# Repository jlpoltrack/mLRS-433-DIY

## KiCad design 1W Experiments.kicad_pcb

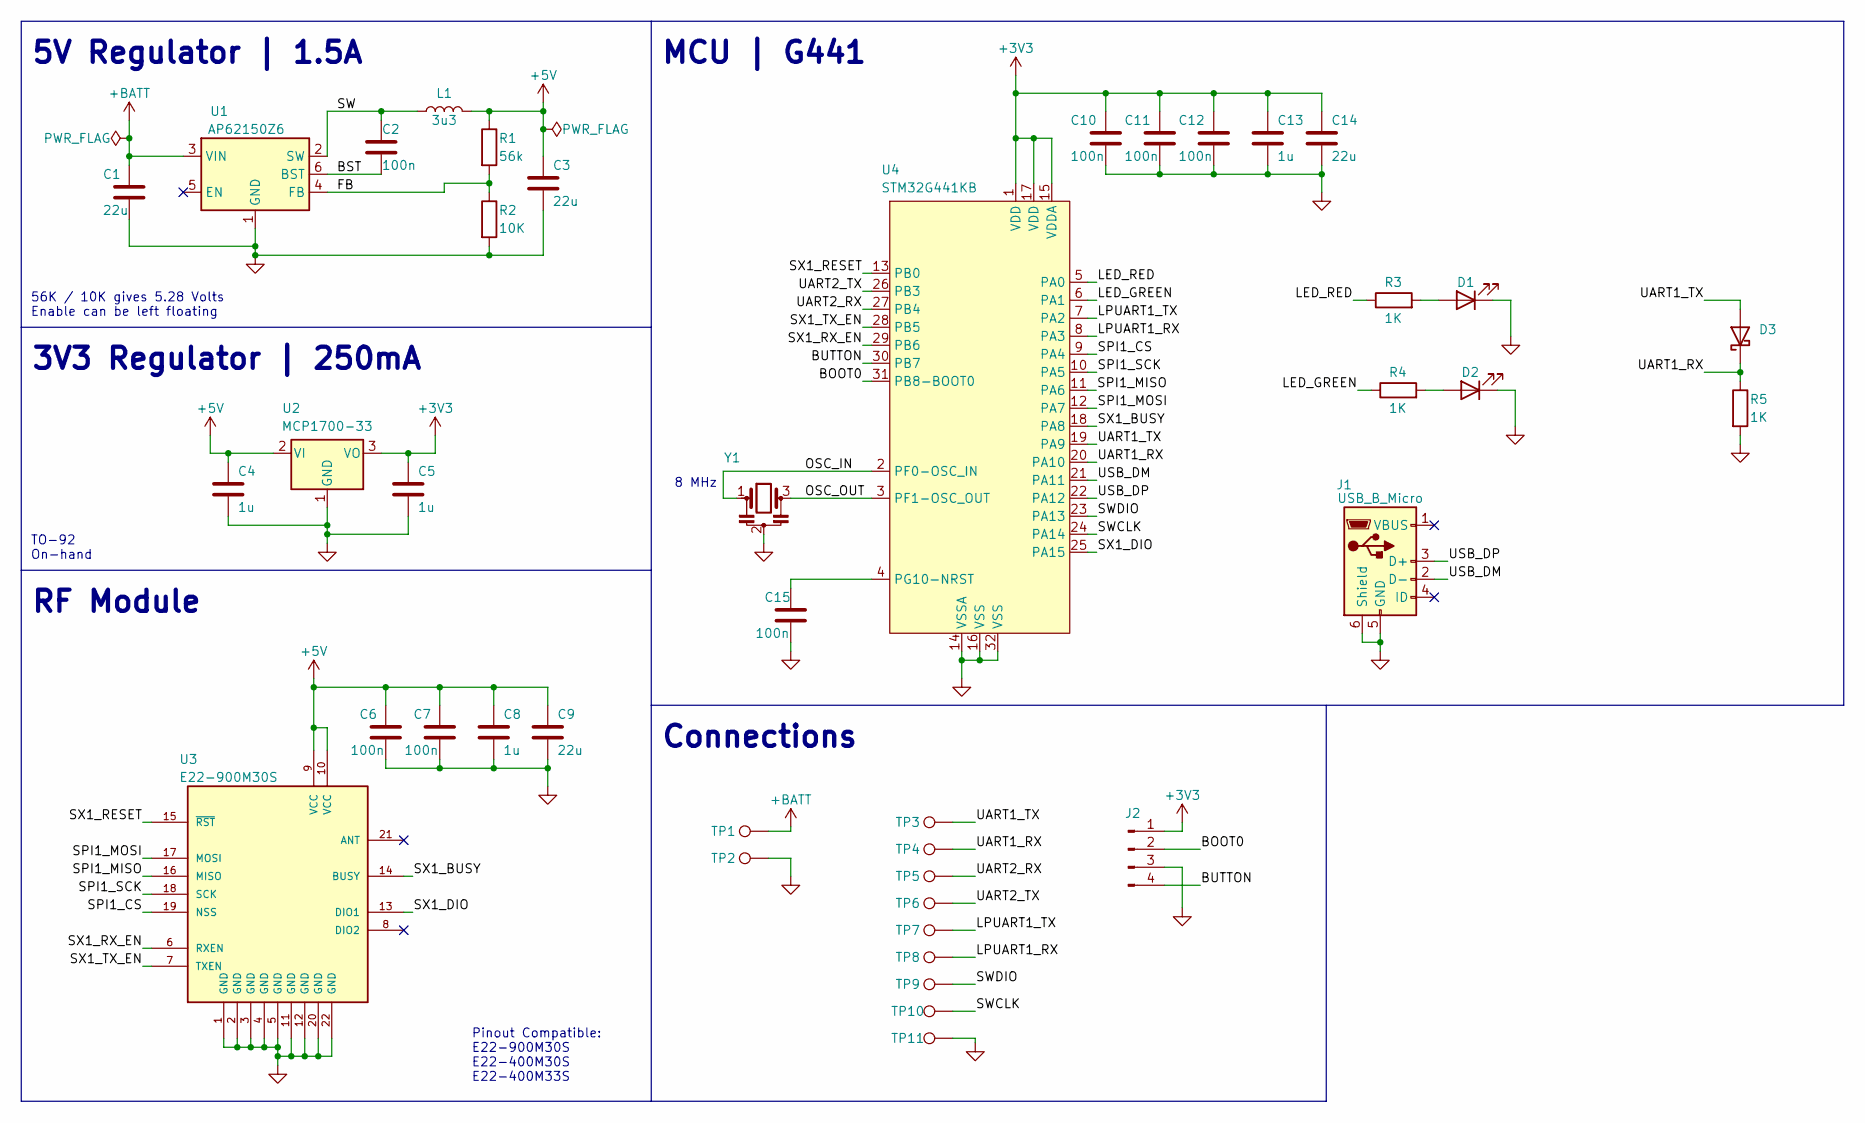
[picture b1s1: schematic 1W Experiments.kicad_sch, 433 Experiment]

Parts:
C1, C3, C9, C14: 22u; C_0805_2012Metric_Pad1.18x1.45mm_HandSolder
C2, C6, C7, C10, C11, C12, C15: 100n; C_0603_1608Metric_Pad1.08x0.95mm_HandSolder
C4, C5, C8, C13: 1u; C_0805_2012Metric_Pad1.18x1.45mm_HandSolder
D1, D2: LED; LED_0603_1608Metric_Pad1.05x0.95mm_HandSolder
D3: D_Schottky; D_SOD-323_HandSoldering
J1: USB_B_Micro; USB_Micro-B_Amphenol_10118194_Horizontal
J2: Conn_01x04_Male; PinHeader_1x04_P2.54mm_Vertical
L1: 3u3; L_1008_2520Metric_Pad1.43x2.20mm_HandSolder
R1: 56k; R_0603_1608Metric_Pad0.98x0.95mm_HandSolder
R2: 10K; R_0603_1608Metric_Pad0.98x0.95mm_HandSolder
R3, R4, R5: 1K; R_0603_1608Metric_Pad0.98x0.95mm_HandSolder
TP1, TP2, TP3, TP4, TP5, TP6, TP7, TP8: TestPoint; TestPoint_Pad_4.0x4.0mm
TP9, TP10, TP11: TestPoint; TestPoint_Pad_D2.5mm
U1: AP62150Z6; TSOT-23-6_HandSoldering
U2: MCP1700-33; TO-92_Inline
U3: E22-900M30S; XCVR_E22-900M30S; PARTREV 1.2
U4: STM32G441KB; LQFP-32_7x7mm_P0.8mm
Y1: Resonator; Resonator_SMD_Murata_CSTxExxV-3Pin_3.0x1.1mm_HandSoldering

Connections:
+3V3: C5.1, C10.1, C11.1, C12.1, C13.1, C14.1, J2.1, U2.3 (VO), U4.1 (VDD), U4.15 (VDDA), U4.17 (VDD)
+5V: C3.1, C4.1, C6.1, C7.1, C8.1, C9.1, L1.2, R1.1, U2.2 (VI), U3.9 (VCC), U3.10 (VCC)
+BATT: C1.1, TP1.1, U1.3 (VIN)
/BOOT0: J2.2, U4.31 (PB8-BOOT0)
/BST: C2.2, U1.6 (BST)
/BUTTON: J2.4, U4.30 (PB7)
/FB: R1.2, R2.1, U1.4 (FB)
/LED_GREEN: R4.1, U4.6 (PA1)
/LED_RED: R3.1, U4.5 (PA0)
/LPUART1_RX: TP8.1, U4.8 (PA3)
/LPUART1_TX: TP7.1, U4.7 (PA2)
/OSC_IN: U4.2 (PF0-OSC_IN), Y1.1
/OSC_OUT: U4.3 (PF1-OSC_OUT), Y1.3
/SPI1_CS: U3.19 (NSS), U4.9 (PA4)
/SPI1_MISO: U3.16 (MISO), U4.11 (PA6)
/SPI1_MOSI: U3.17 (MOSI), U4.12 (PA7)
/SPI1_SCK: U3.18 (SCK), U4.10 (PA5)
/SW: C2.1, L1.1, U1.2 (SW)
/SWCLK: TP10.1, U4.24 (PA14)
/SWDIO: TP9.1, U4.23 (PA13)
/SX1_BUSY: U3.14 (BUSY), U4.18 (PA8)
/SX1_DIO: U3.13 (DIO1), U4.25 (PA15)
/SX1_RESET: U3.15 (~RST), U4.13 (PB0)
/SX1_RX_EN: U3.6 (RXEN), U4.29 (PB6)
/SX1_TX_EN: U3.7 (TXEN), U4.28 (PB5)
/UART1_RX: D3.1 (K), R5.1, TP4.1, U4.20 (PA10)
/UART1_TX: D3.2 (A), TP3.1, U4.19 (PA9)
/UART2_RX: TP5.1, U4.27 (PB4)
/UART2_TX: TP6.1, U4.26 (PB3)
/USB_DM: J1.2 (D-), U4.21 (PA11)
/USB_DP: J1.3 (D+), U4.22 (PA12)
GND: C1.2, C3.2, C4.2, C5.2, C6.2, C7.2, C8.2, C9.2, C10.2, C11.2, C12.2, C13.2, C14.2, C15.2, D1.1 (K), D2.1 (K), J1.5 (GND), J1.6 (Shield), J2.3, R2.2, R5.2, TP2.1, TP11.1, U1.1 (GND), U2.1 (GND), U3.1 (GND), U3.2 (GND), U3.3 (GND), U3.4 (GND), U3.5 (GND), U3.11 (GND), U3.12 (GND), U3.20 (GND), U3.22 (GND), U4.14 (VSSA), U4.16 (VSS), U4.32 (VSS), Y1.2
unnamed: C15.1, U4.4 (PG10-NRST)
unnamed: D1.2 (A), R3.2
unnamed: D2.2 (A), R4.2

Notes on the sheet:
56K / 10K gives 5.28 Volts Enable can be left floating
Connections
Pinout Compatible: E22-900M30S E22-400M30S E22-400M33S
5V Regulator | 1.5A
3V3 Regulator | 250mA
8 MHz
MCU | G441
RF Module
TO-92 On-hand

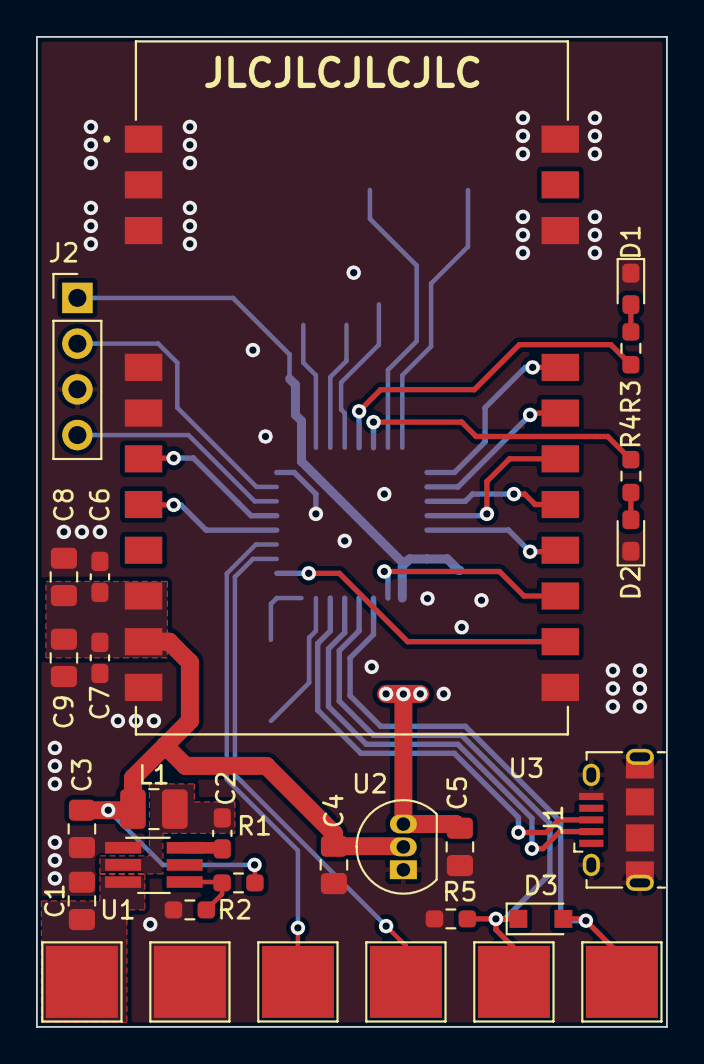
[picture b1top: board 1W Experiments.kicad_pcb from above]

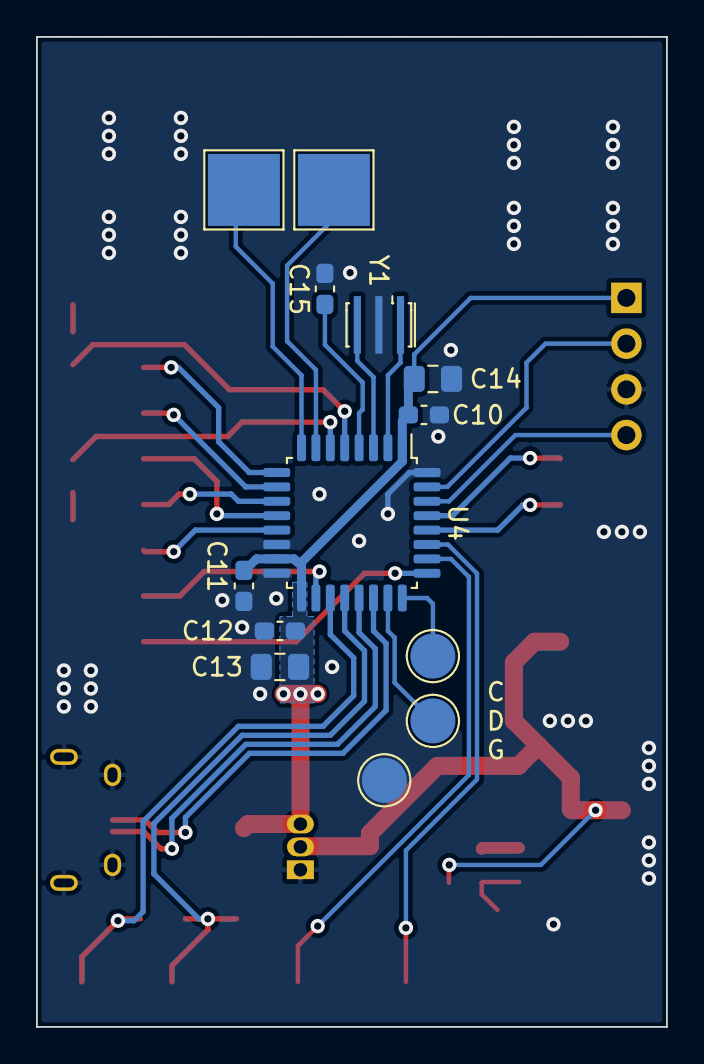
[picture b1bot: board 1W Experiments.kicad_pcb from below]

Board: 2 copper layers, 35.0 x 55.0 mm, 42 parts (13 on the bottom side), 35 nets.

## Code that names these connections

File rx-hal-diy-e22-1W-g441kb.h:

//*******************************************************
// Copyright (c) MLRS project
// GPL3
// https://www.gnu.org/licenses/gpl-3.0.de.html
// OlliW @ www.olliw.eu
//*******************************************************
// hal
//********************************************************

//-------------------------------------------------------
// RX DIY E22 v007 STM32G441KB
//-------------------------------------------------------

#define DEVICE_HAS_OUT


//-- Timers, Timing, EEPROM, and such stuff

#define DELAY_USE_DWT

#define SYSTICK_TIMESTEP          1000
#define SYSTICK_DELAY_MS(x)       (uint16_t)(((uint32_t)(x)*(uint32_t)1000)/SYSTICK_TIMESTEP)

#define EE_START_PAGE             60 // 128 kB flash, 2 kB page


//-- UARTS
// UARTB = serial port
// UART = output port, SBus or whatever
// UARTC = debug port

#define UARTB_USE_UART2_REMAPPED2 // serial
#define UARTB_BAUD                TX_SERIAL_BAUDRATE
#define UARTB_USE_TX
#define UARTB_TXBUFSIZE           TX_SERIAL_TXBUFSIZE
#define UARTB_USE_TX_ISR
#define UARTB_USE_RX
#define UARTB_RXBUFSIZE           TX_SERIAL_RXBUFSIZE
//#define UARTB_USE_RX_IO           IO_PA15 // normally would be PB4!!  Fixed in hardware

#define UART_USE_UART1                      // out pin
#define UART_BAUD                 100000    // SBus normal baud rate, is being set later anyhow
#define UART_USE_TX
#define UART_TXBUFSIZE            256       // 512
#define UART_USE_TX_ISR
//#define UART_USE_RX
//#define UART_RXBUFSIZE            512

#define UARTC_USE_LPUART1 // debug
#define UARTC_BAUD                115200
#define UARTC_USE_TX
#define UARTC_TXBUFSIZE           512
#define UARTC_USE_TX_ISR
//#define UARTC_USE_RX
//#define UARTC_RXBUFSIZE           512


//-- SX1: SX12xx & SPI

#define SPI_USE_SPI1              // PA5, PA6, PA7
#define SPI_CS_IO                 IO_PA4
#define SPI_USE_CLK_LOW_1EDGE     // datasheet says CPHA = 0  CPOL = 0
#define SPI_USE_CLOCKSPEED_9MHZ

#define SX_RESET                  IO_PB0
#define SX_DIO1                   IO_PB4
#define SX_BUSY                   IO_PA8
#define SX_RX_EN                  IO_PB6
#define SX_TX_EN                  IO_PB5

#define SX_DIO1_SYSCFG_EXTI_PORTx     LL_SYSCFG_EXTI_PORTB
#define SX_DIO1_SYSCFG_EXTI_LINEx     LL_SYSCFG_EXTI_LINE4
#define SX_DIO_EXTI_LINE_x            LL_EXTI_LINE_4
#define SX_DIO_EXTI_IRQn              EXTI4_IRQn
#define SX_DIO_EXTI_IRQHandler        EXTI4_IRQHandler
//#define SX_DIO_EXTI_IRQ_PRIORITY    11

void sx_init_gpio(void)
{
    gpio_init(SX_RESET, IO_MODE_OUTPUT_PP_HIGH, IO_SPEED_VERYFAST);
    gpio_init(SX_DIO1, IO_MODE_INPUT_PD, IO_SPEED_VERYFAST);
    gpio_init(SX_BUSY, IO_MODE_INPUT_PU, IO_SPEED_VERYFAST);
    gpio_init(SX_TX_EN, IO_MODE_OUTPUT_PP_LOW, IO_SPEED_VERYFAST);
    gpio_init(SX_RX_EN, IO_MODE_OUTPUT_PP_LOW, IO_SPEED_VERYFAST);
}

bool sx_busy_read(void)
{
    return (gpio_read_activehigh(SX_BUSY)) ? true : false;
}

void sx_amp_transmit(void)
{
    gpio_low(SX_RX_EN);
    gpio_high(SX_TX_EN);
}

void sx_amp_receive(void)
{
    gpio_low(SX_TX_EN);
    gpio_high(SX_RX_EN);
}

void sx_dio_init_exti_isroff(void)
{
    LL_SYSCFG_SetEXTISource(SX_DIO1_SYSCFG_EXTI_PORTx, SX_DIO1_SYSCFG_EXTI_LINEx);

    // let's not use LL_EXTI_Init(), but let's do it by hand, is easier to allow enabling isr later
    LL_EXTI_DisableEvent_0_31(SX_DIO_EXTI_LINE_x);
    LL_EXTI_DisableIT_0_31(SX_DIO_EXTI_LINE_x);
    LL_EXTI_DisableFallingTrig_0_31(SX_DIO_EXTI_LINE_x);
    LL_EXTI_EnableRisingTrig_0_31(SX_DIO_EXTI_LINE_x);

    NVIC_SetPriority(SX_DIO_EXTI_IRQn, SX_DIO_EXTI_IRQ_PRIORITY);
    NVIC_EnableIRQ(SX_DIO_EXTI_IRQn);
}

void sx_dio_enable_exti_isr(void)
{
    LL_EXTI_ClearFlag_0_31(SX_DIO_EXTI_LINE_x);
    LL_EXTI_EnableIT_0_31(SX_DIO_EXTI_LINE_x);
}

void sx_dio_exti_isr_clearflag(void)
{
    LL_EXTI_ClearFlag_0_31(SX_DIO_EXTI_LINE_x);
}


//-- Out port
#ifdef UART_USE_UART2
  #define OUT_UARTx               USART2
#elif defined UART_USE_LPUART1
  #define OUT_UARTx               LPUART1
#elif defined UART_USE_UART1
  #define OUT_UARTx               USART1
#endif


void out_init_gpio(void)
{
}

void out_set_normal(void)
{
    LL_USART_Disable(OUT_UARTx);
    LL_USART_SetTXPinLevel(OUT_UARTx, LL_USART_TXPIN_LEVEL_STANDARD);
    LL_USART_Enable(OUT_UARTx);
}

void out_set_inverted(void)
{
    LL_USART_Disable(OUT_UARTx);
    LL_USART_SetTXPinLevel(OUT_UARTx, LL_USART_TXPIN_LEVEL_INVERTED);
    LL_USART_Enable(OUT_UARTx);
}


//-- Button

#define BUTTON                    IO_PB7

void button_init(void)
{
    gpio_init(BUTTON, IO_MODE_INPUT_PU, IO_SPEED_DEFAULT);
}

bool button_pressed(void)
{
    return gpio_read_activelow(BUTTON);
}


//-- LEDs

#define LED_GREEN 		            IO_PA1
#define LED_RED		                IO_PA0

void leds_init(void)
{
    gpio_init(LED_GREEN, IO_MODE_OUTPUT_PP_LOW, IO_SPEED_DEFAULT);
    gpio_init(LED_RED, IO_MODE_OUTPUT_PP_LOW, IO_SPEED_DEFAULT);
    gpio_low(LED_GREEN); // LED_GREEN_OFF
    gpio_low(LED_RED); // LED_RED_OFF
}

void led_green_off(void) { gpio_low(LED_GREEN); }
void led_green_on(void) { gpio_high(LED_GREEN); }
void led_green_toggle(void) { gpio_toggle(LED_GREEN); }

void led_red_off(void) { gpio_low(LED_RED); }
void led_red_on(void) { gpio_high(LED_RED); }
void led_red_toggle(void) { gpio_toggle(LED_RED); }


//-- POWER

#define POWER_GAIN_DBM            13 // gain of a PA stage if present
#define POWER_SX126X_MAX_DBM      SX126X_POWER_20_DBM // maximum allowed sx power
#define POWER_USE_DEFAULT_RFPOWER_CALC

#define RFPOWER_DEFAULT           1 // index into rfpower_list array

const rfpower_t rfpower_list[] = {
	{ .dbm = POWER_10_DBM, .mW = 10 },
	{ .dbm = POWER_20_DBM, .mW = 100 },
	{ .dbm = POWER_24_DBM, .mW = 250 },
	{ .dbm = POWER_27_DBM, .mW = 500 },
	{ .dbm = POWER_30_DBM, .mW = 1000 },
};

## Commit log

2023-05-28 Initial
2023-05-28 Fixed schematic
